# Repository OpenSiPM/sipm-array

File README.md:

# sipm-array
Schematics and layouts for SiPM arrays

# tia-s14160-x4
This contains schematics and PCB layouts for a 4 channel SiPM detection board used for parallel laser scanning.  Each channel implements the standard OpenSiPM transimpedance amplifier, pole zero cancelation, and low pass filtering to produce a Gaussian single photon response.  

# impulse response

# power supply
The X4 design uses the standard OpenSiPM power supply and bias generator boards.  Due to the higher current from running 4 SiPMs in parallel, the LT8362 bias generator is recommended for maximum dynamic range, although both designs will work.  Additionally the board can be configured to use two separate power supplies by ommitting resistors and plugging in two supply boards to both sockets.  However, in normal useage this is not required and is probably not useful as the current demand is low enough that a single supply is adquate.

# Non-descanned detection arm
Zemax simulation for non-descanned detection using the 4 channel SiPM board and the prescription for the lens array used can be found [here](https://github.com/OpenSiPM/sipm-array/tree/main/Zemax). 

# publication
A manuscript is forthcoming.

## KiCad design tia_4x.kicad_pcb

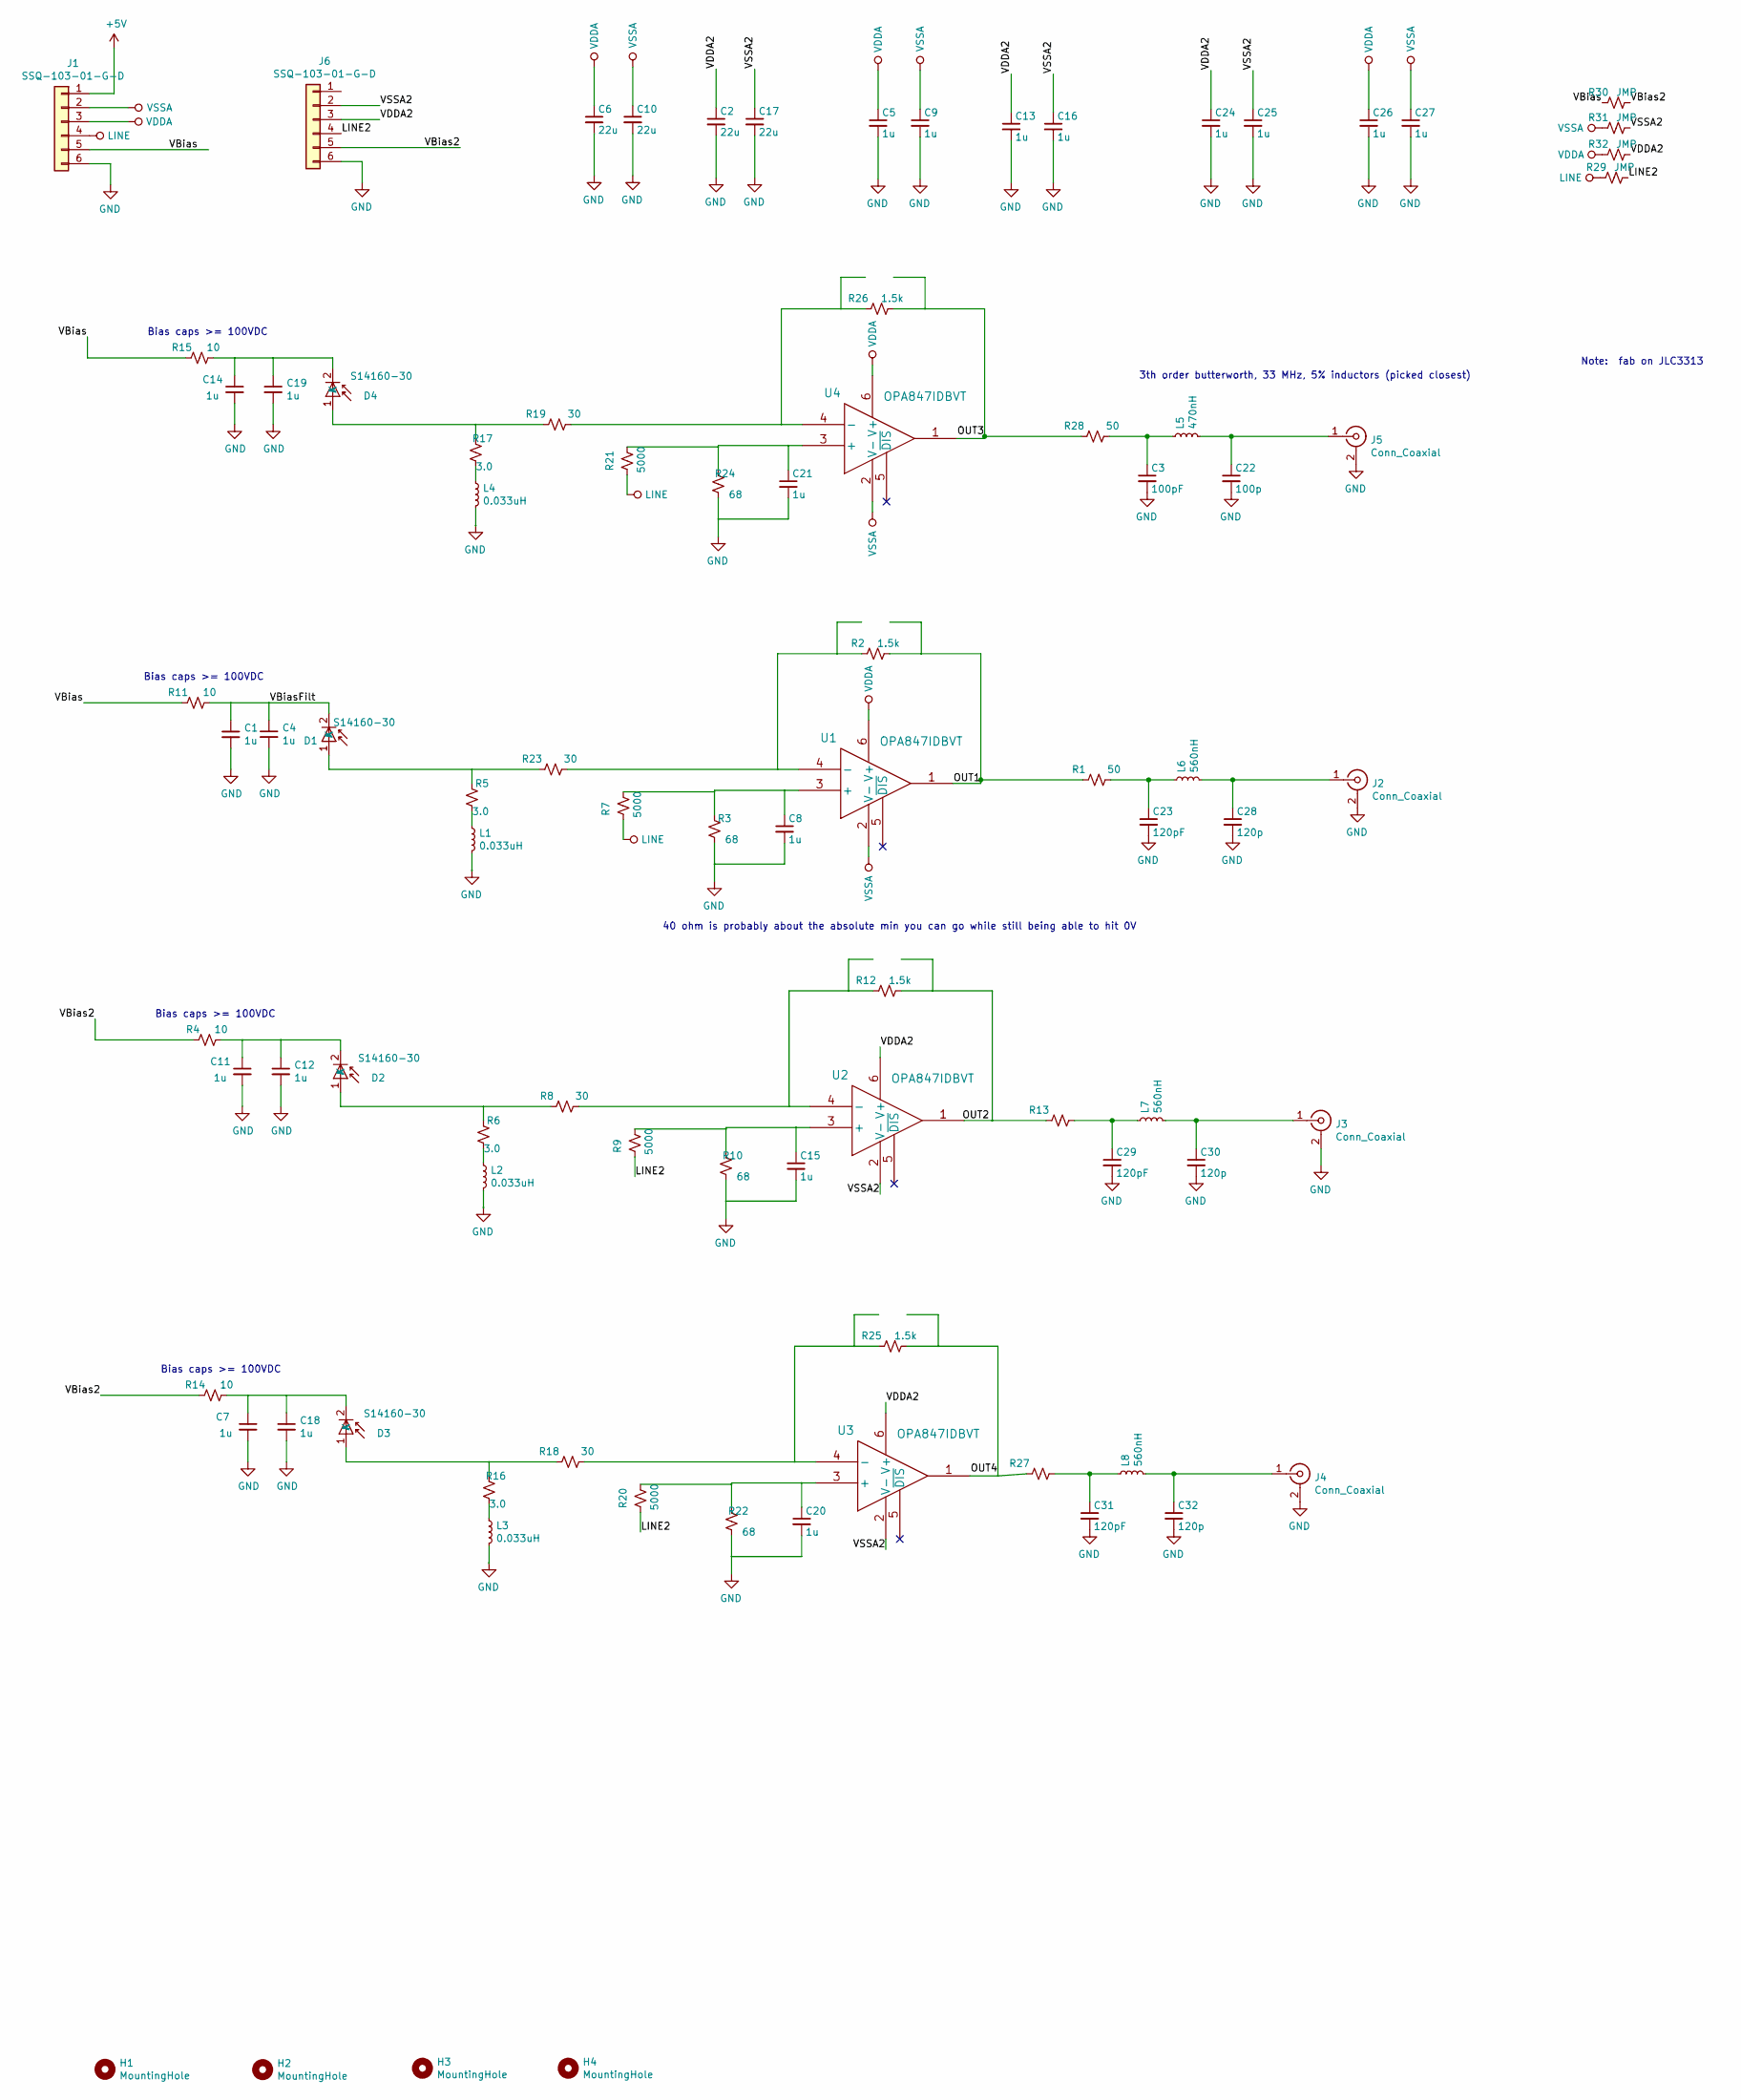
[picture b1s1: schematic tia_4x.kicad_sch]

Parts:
C1, C4, C7, C11, C12, C14, C18, C19: 1u; C_1206_3216Metric
C2, C6, C10, C17: 22u; C_0603_1608Metric
C3: 100pF; C_0402_1005Metric
C5, C8, C9, C13, C15, C16, C20, C21, C24, C25, C26, C27: 1u; C_0402_1005Metric
C22: 100p; C_0402_1005Metric
C23, C29, C31: 120pF; C_0402_1005Metric
C28, C30, C32: 120p; C_0402_1005Metric
D1, D2, D3, D4: S14160-30
H1, H2, H3, H4: MountingHole; MountingHole_6mm
J1, J6: SSQ-103-01-G-D; PinHeader_2x03_P2.54mm_Vertical
J2, J3, J4, J5: Conn_Coaxial; SMB_Jack_Vertical; Digikey WM5528-ND
L1, L2, L3, L4: 0.033uH; L_0603_1608Metric
L5: 470nH; L_0402_1005Metric; part MLF1005GR56JTD25
L6, L7, L8: 560nH; L_0402_1005Metric; part MLF1005GR56JTD25
R1, R13, R27, R28: 50; R_0402_1005Metric
R2, R12, R25, R26: 1.5k; R_0402_1005Metric
R3, R10, R22, R24: 68; R_0402_1005Metric
R4, R11, R14, R15: 10; R_0402_1005Metric
R5, R6, R16, R17: 3.0; R_0402_1005Metric
R7, R9, R20, R21: 5000; R_0402_1005Metric
R8, R18, R19, R23: 30; R_0402_1005Metric
R29, R30, R31, R32: JMP; R_0402_1005Metric
U1, U2, U3, U4: OPA847IDBVT

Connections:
+5V: J1.1
/LINE2: J6.4, R9.2, R20.2, R29.2
/OUT1: R1.1, R2.2, U1.1
/OUT2: R12.2, R13.1, U2.1
/OUT3: R26.2, R28.1, U4.1
/OUT4: R25.2, R27.1, U3.1
/VBias: J1.5, R11.1, R15.1, R30.1
/VBias2: J6.5, R4.1, R14.1, R30.2
/VBiasFilt: C1.1, C4.1, D1.2 (K), R11.2
/VDDA2: C2.1, C13.1, C24.1, J6.3, R32.2, U2.6 (V+), U3.6 (V+)
/VSSA2: C16.1, C17.1, C25.1, J6.2, R31.2, U2.2 (V-), U3.2 (V-)
GND: C1.2, C2.2, C3.2, C4.2, C5.2, C6.2, C7.2, C8.2, C9.2, C10.2, C11.2, C12.2, C13.2, C14.2, C15.2, C16.2, C17.2, C18.2, C19.2, C20.2, C21.2, C22.2, C23.2, C24.2, C25.2, C26.2, C27.2, C28.2, C29.2, C30.2, C31.2, C32.2, J1.6, J2.2 (Ext), J3.2 (Ext), J4.2 (Ext), J5.2 (Ext), J6.6, L1.2, L2.2, L3.2, L4.2, R3.1, R10.1, R22.1, R24.1
LINE: J1.4, R7.2, R21.2, R29.1
unnamed: C3.1, L5.1, R28.2
unnamed: C23.1, L6.1, R1.2
unnamed: C29.1, L7.1, R13.2
unnamed: C31.1, L8.1, R27.2
unnamed: D1.1 (A), R5.2, R23.1
unnamed: D2.1 (A), R6.2, R8.1
unnamed: C11.1, C12.1, D2.2 (K), R4.2
unnamed: D3.1 (A), R16.2, R18.1
unnamed: C7.1, C18.1, D3.2 (K), R14.2
unnamed: D4.1 (A), R17.2, R19.1
unnamed: C14.1, C19.1, D4.2 (K), R15.2
unnamed: C28.1, J2.1 (In), L6.2
unnamed: C30.1, J3.1 (In), L7.2
unnamed: C32.1, J4.1 (In), L8.2
unnamed: C22.1, J5.1 (In), L5.2
unnamed: L1.1, R5.1
unnamed: L2.1, R6.1
unnamed: L3.1, R16.1
unnamed: L4.1, R17.1
unnamed: C8.1, R3.2, R7.1, U1.3 (+)
unnamed: R2.1, R23.2, U1.4 (-)
unnamed: C15.1, R9.1, R10.2, U2.3 (+)
unnamed: R8.2, R12.1, U2.4 (-)
unnamed: C20.1, R20.1, R22.2, U3.3 (+)
unnamed: R18.2, R25.1, U3.4 (-)
unnamed: C21.1, R21.1, R24.2, U4.3 (+)
unnamed: R19.2, R26.1, U4.4 (-)
VDDA: C5.1, C6.1, C26.1, J1.3, R32.1, U1.6 (V+), U4.6 (V+)
VSSA: C9.1, C10.1, C27.1, J1.2, R31.1, U1.2 (V-), U4.2 (V-)

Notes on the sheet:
40 ohm is probably about the absolute min you can go while still being able to hit 0V
Bias caps >= 100VDC
3th order butterworth, 33 MHz, 5% inductors (picked closest)
Note: fab on JLC3313

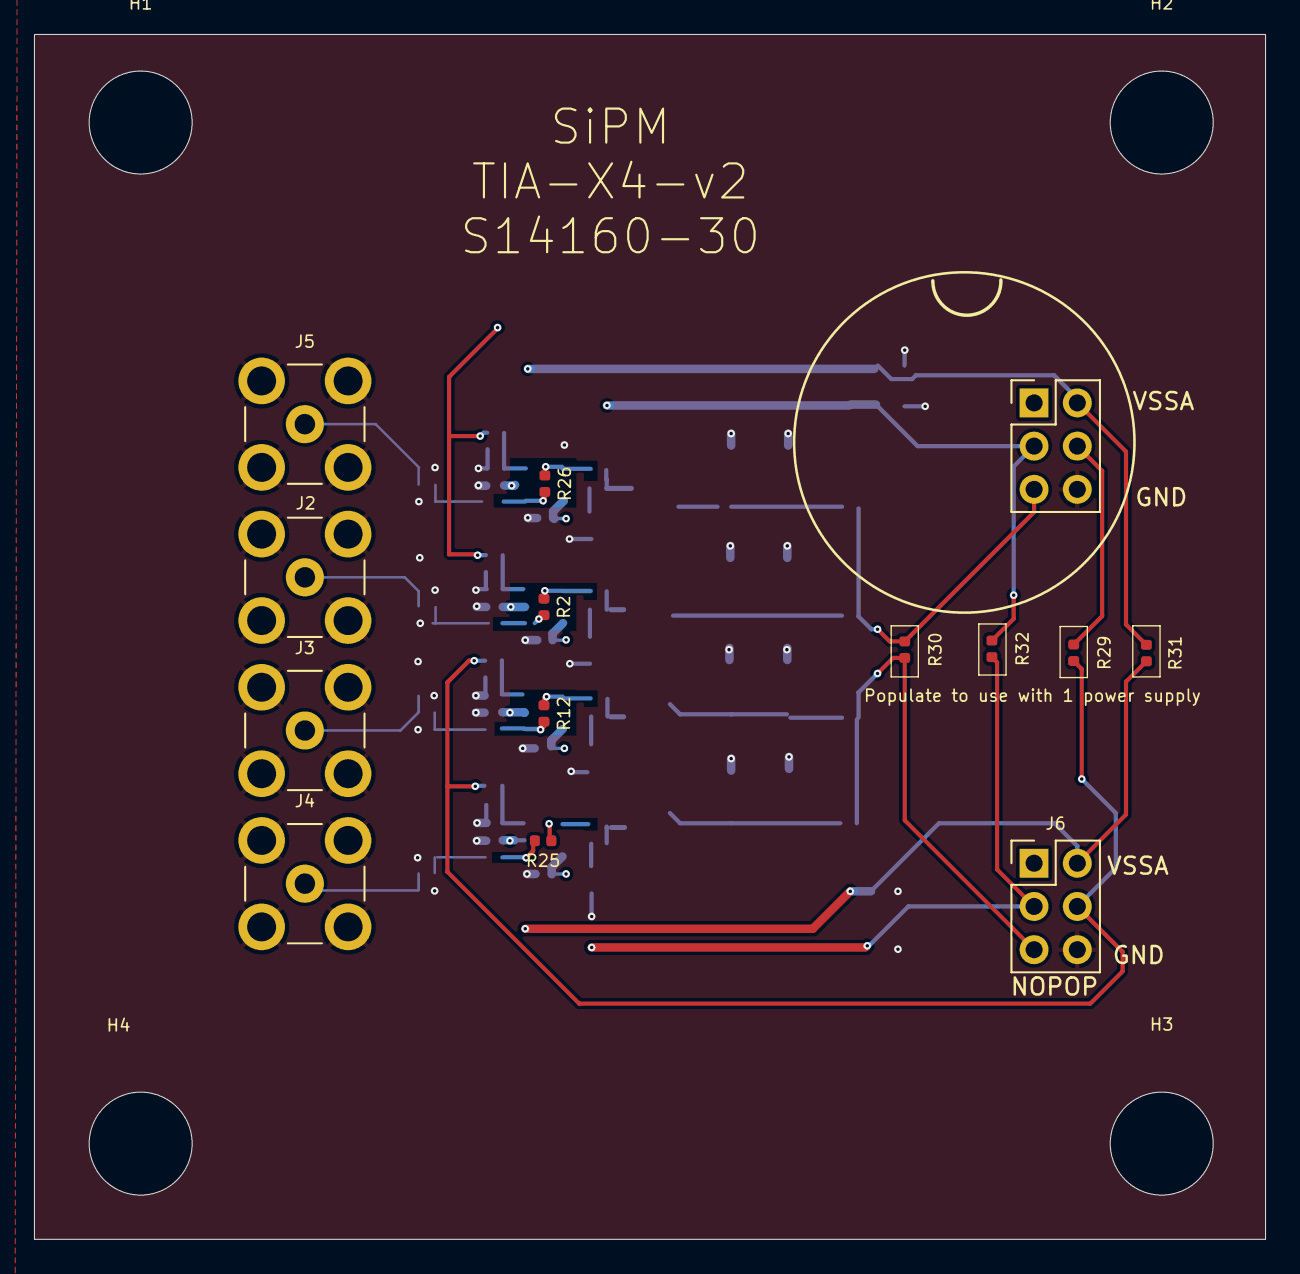
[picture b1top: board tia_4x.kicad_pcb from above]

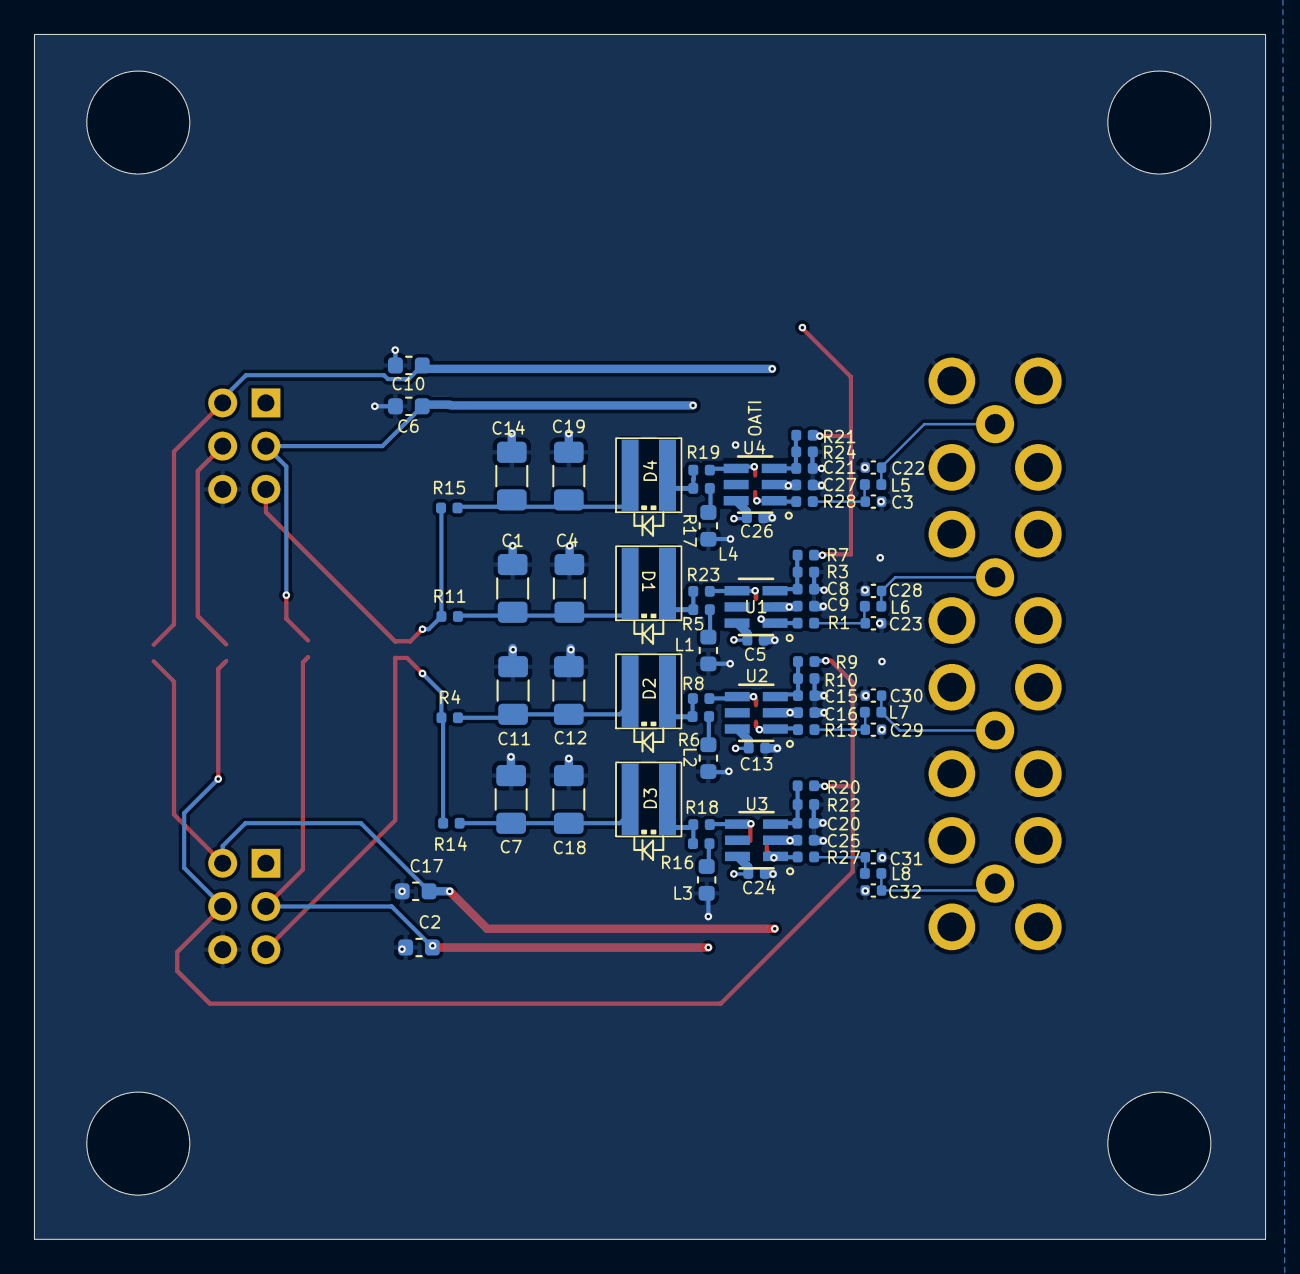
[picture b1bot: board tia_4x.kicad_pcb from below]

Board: 4 copper layers, 72.3 x 70.8 mm, 90 parts (72 on the bottom side), 41 nets.

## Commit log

2024-12-06 Initial upload for 4x SiPM board for parallel scanning
2025-05-05 Add Zemax simulation files for the non descanned detection arm and the lens array prescription
2025-05-05 Update README.md
    updated readme to include a link to the non-descanned detection arm design and simulation

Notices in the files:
parts and their libraries:
Copyright 2016 Accelerated Designs. All rights reserved.
